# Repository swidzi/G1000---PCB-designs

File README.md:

# G1000 - PCB-desgins
PCB designes for G1000 Flight Sim controller STL (3d) files made by FlightSimMaker

This repository contains Eagle files for the PCB designed for G1000. All PCBs are millable on single sided clad with a 3018Pro CNC router.
Board design can be changed at anytime.
Boards are designed to be interconnected - if used separately they will probably not work.

# G1000 PFD/MFD PCB interconnection chart

# G1000 Audio PanelPCB interconnection chart

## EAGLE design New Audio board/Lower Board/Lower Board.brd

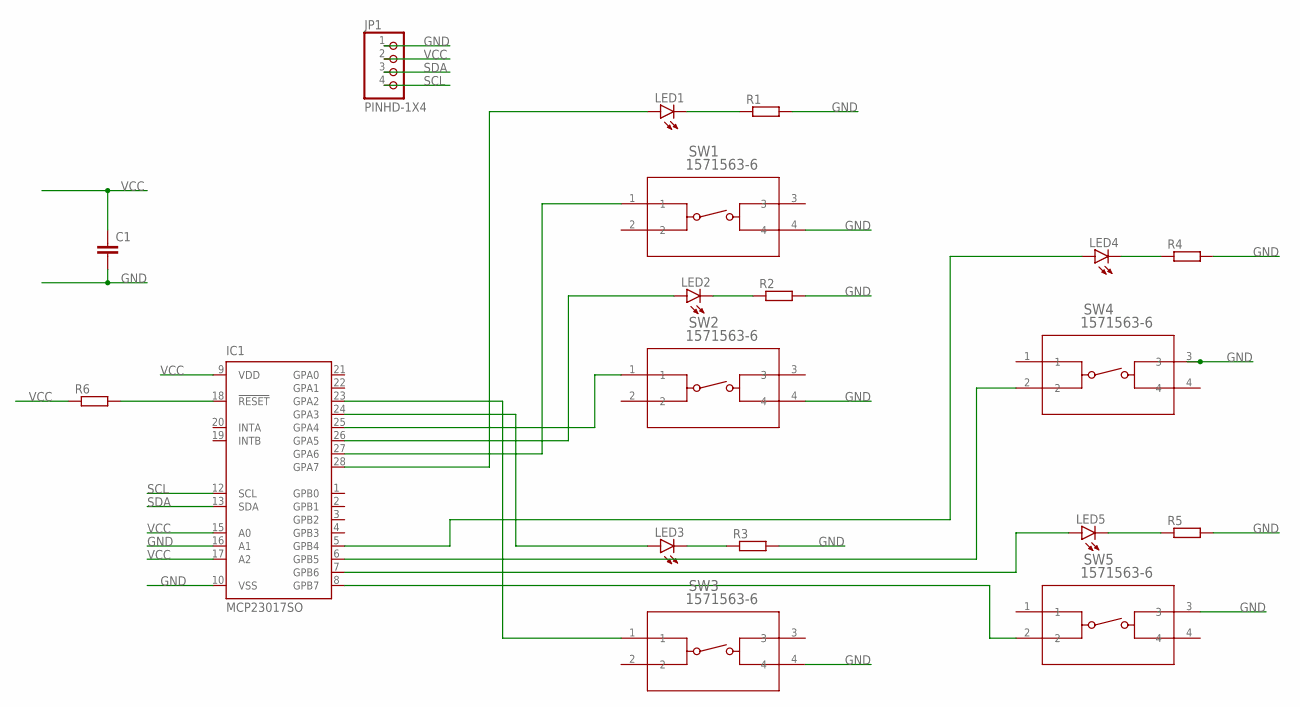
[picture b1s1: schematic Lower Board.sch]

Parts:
C1: C-EU025-025X050; C025-025X050
IC1: MCP23017SO; SO28W
JP1: PINHD-1X4; 1X04
LED1, LED2, LED3, LED4, LED5: LEDCHIP-LED0805; CHIP-LED0805
R1, R2, R3, R4, R5, R6: R-EU_R0805; R0805
SW1, SW2, SW3, SW4, SW5: 1571563-6; SW4_1437565-E

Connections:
GND: C1.2, IC1.10 (VSS), IC1.16 (A1), JP1.1, R1.2, R2.2, R3.2, R4.2, R5.2, SW1.4, SW2.4, SW3.4, SW4.3, SW5.3
unnamed: LED1.C, R1.1
unnamed: LED2.C, R2.1
unnamed: LED3.C, R3.1
unnamed: LED5.C, R5.1
unnamed: LED4.C, R4.1
unnamed: IC1.28 (GPA7), LED1.A
unnamed: IC1.27 (GPA6), SW1.1
unnamed: IC1.26 (GPA5), LED2.A
unnamed: IC1.25 (GPA4), SW2.1
unnamed: IC1.24 (GPA3), LED3.A
unnamed: IC1.23 (GPA2), SW3.1
unnamed: IC1.8 (GPB7), SW5.2
unnamed: IC1.18 (!RESET), R6.2
unnamed: IC1.7 (GPB6), LED5.A
unnamed: IC1.6 (GPB5), SW4.2
unnamed: IC1.5 (GPB4), LED4.A
SCL: IC1.12 (SCL), JP1.4
SDA: IC1.13 (SDA), JP1.3
VCC: C1.1, IC1.9 (VDD), IC1.15 (A0), IC1.17 (A2), JP1.2, R6.1

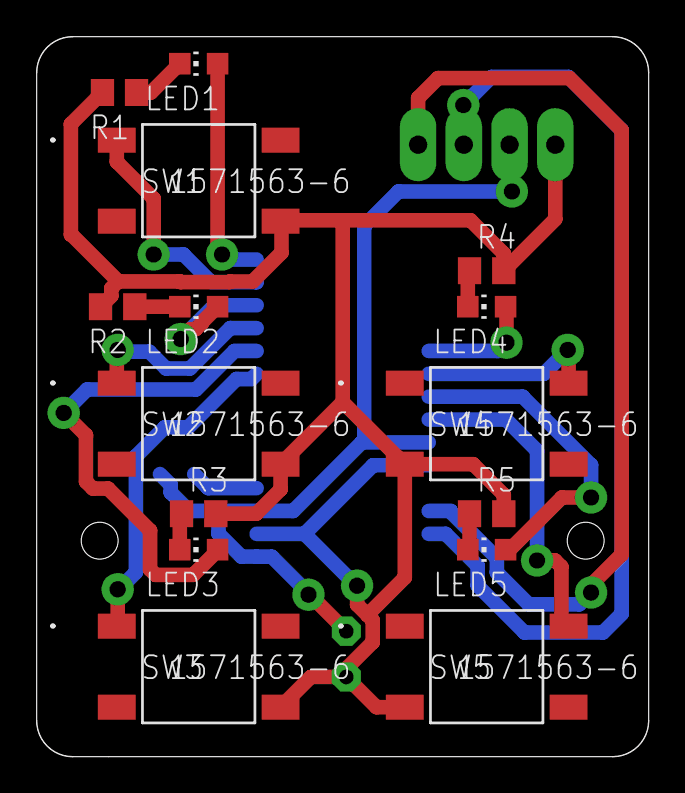
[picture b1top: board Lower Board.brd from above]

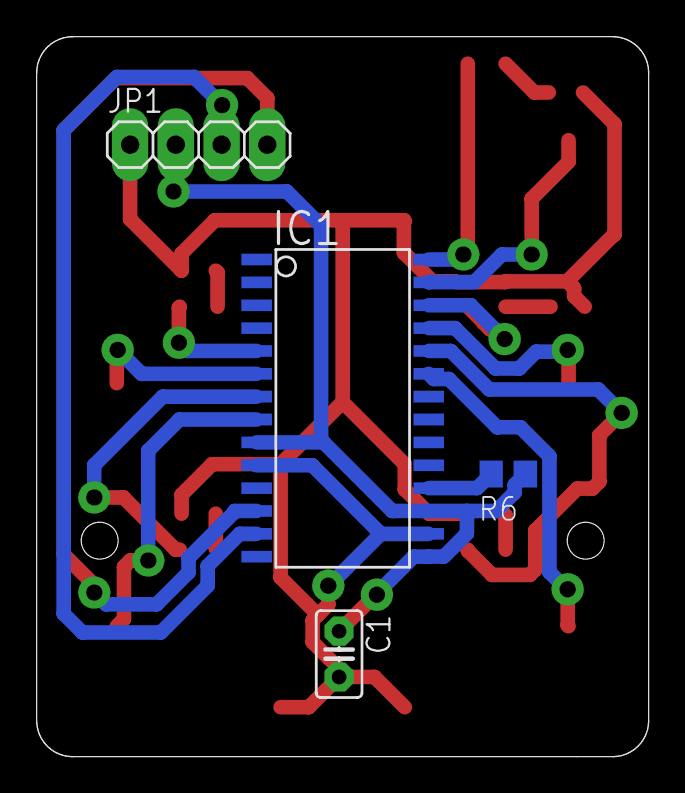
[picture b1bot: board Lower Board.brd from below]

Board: 2 copper layers, 34.0 x 40.0 mm, 19 parts (4 on the bottom side), 20 nets.

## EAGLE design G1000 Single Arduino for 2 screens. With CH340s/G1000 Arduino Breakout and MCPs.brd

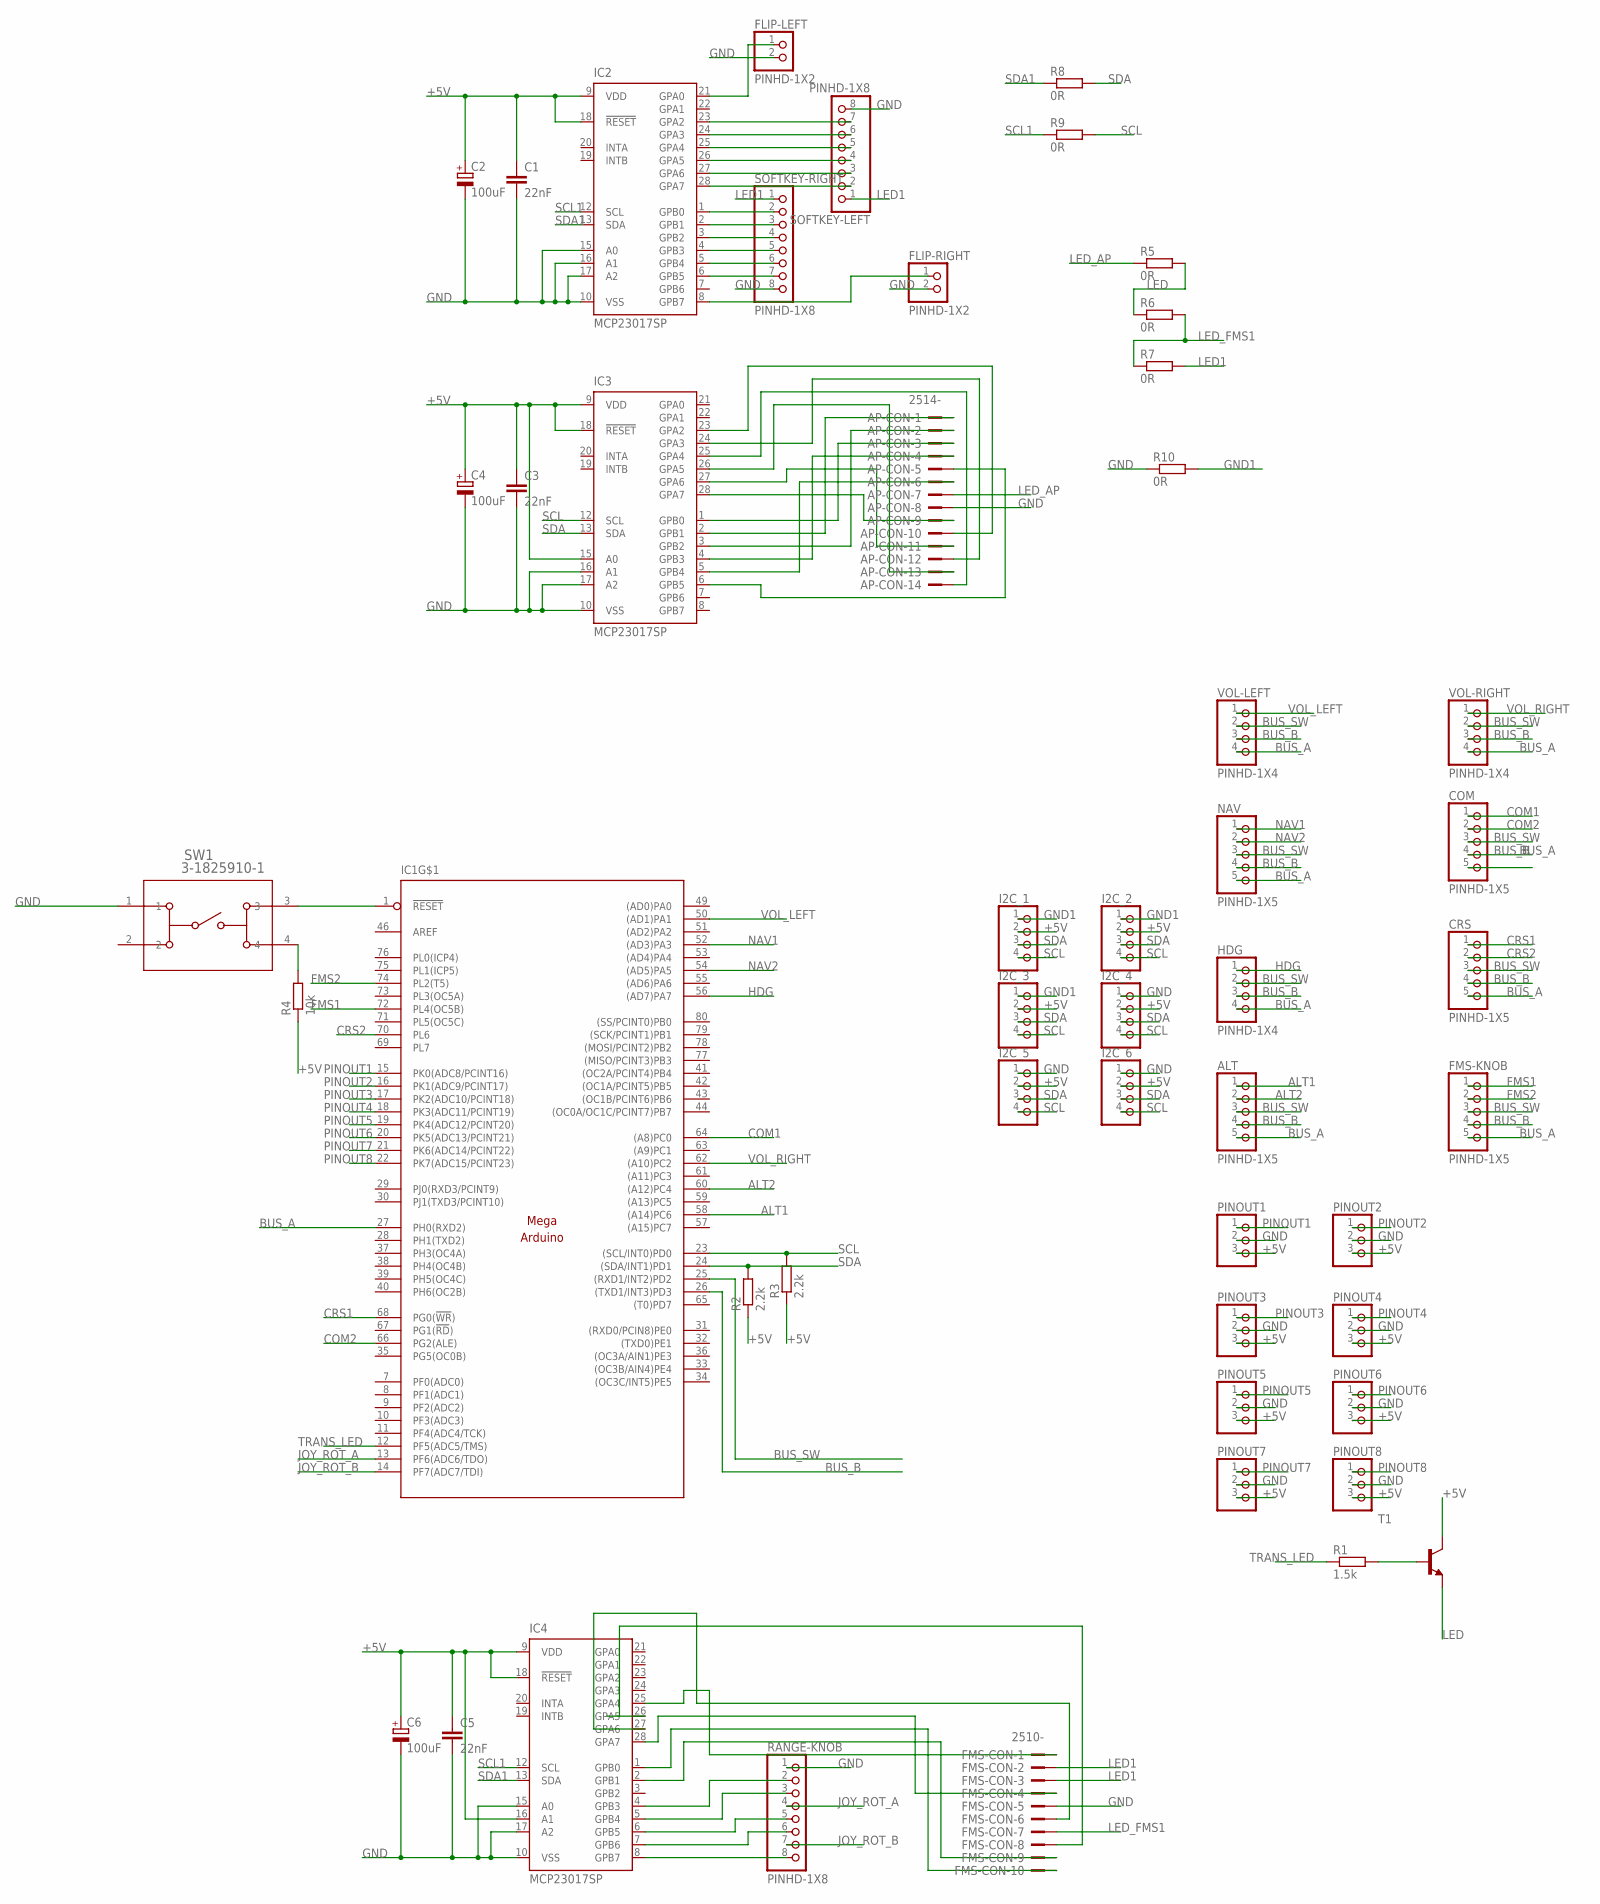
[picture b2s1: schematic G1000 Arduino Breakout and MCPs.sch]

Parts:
ALT: PINHD-1X5; 1X05
AP-CON: 2514-; PAK100/2500-14
C1, C3, C5: 22nF; C025-025X050
C2, C4, C6: 100uF; E2,5-6
COM: PINHD-1X5; 1X05
CRS: PINHD-1X5; 1X05
FLIP-LEFT: PINHD-1X2; 1X02
FLIP-RIGHT: PINHD-1X2; 1X02
FMS-CON: 2510-; PAK100/2500-10
FMS-KNOB: PINHD-1X5; 1X05
HDG: PINHD-1X4; 1X04
I2C_1, I2C_2, I2C_3, I2C_4, I2C_5, I2C_6: PINHD-1X4; 1X04
IC1: MEGAARDUINO_22; MEGA_ARDUINO_2
IC2, IC3, IC4: MCP23017SP; DIL28-3
NAV: PINHD-1X5; 1X05
PINOUT1, PINOUT2, PINOUT3, PINOUT4, PINOUT5, PINOUT6, PINOUT7, PINOUT8: PINHD-1X3; 1X03
R1: 1.5k; 0207/10
R2, R3: 2.2k; 0207/10
R4: 10k; 0207/10
R5, R6, R7, R8, R9, R10: 0R; 0207/10
RANGE-KNOB: PINHD-1X8; 1X08
SOFTKEY-LEFT: PINHD-1X8; 1X08
SOFTKEY-RIGHT: PINHD-1X8; 1X08
SW1: 3-1825910-1; SW4_1825910-H
T1: 2N2222-NPN-TO92-EBC; TO92-EBC
VOL-LEFT: PINHD-1X4; 1X04
VOL-RIGHT: PINHD-1X4; 1X04

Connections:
+3V3: IC1.2 (+3V3)
+5V: C1.1, C2.+, C3.1, C4.+, C5.1, C6.+, I2C_1.2, I2C_2.2, I2C_3.2, I2C_4.2, I2C_5.2, I2C_6.2, IC1.3 (+5V), IC1.47 (+5V), IC1.48 (+5V), IC2.9 (VDD), IC2.18 (!RESET), IC3.9 (VDD), IC3.15 (A0), IC3.18 (!RESET), IC4.9 (VDD), IC4.16 (A1), IC4.18 (!RESET), PINOUT1.3, PINOUT2.3, PINOUT3.3, PINOUT4.3, PINOUT5.3, PINOUT6.3, PINOUT7.3, PINOUT8.3, R2.1, R3.1, R4.1, T1.C
+VIN: IC1.6 (+VIN)
ALT1: ALT.1, IC1.58 ((A14)PC6)
ALT2: ALT.2, IC1.60 ((A12)PC4)
BUS_A: ALT.5, COM.5, CRS.5, FMS-KNOB.5, HDG.4, IC1.27 (PH0(RXD2)), NAV.5, VOL-LEFT.4, VOL-RIGHT.4
BUS_B: ALT.4, COM.4, CRS.4, FMS-KNOB.4, HDG.3, IC1.26 ((TXD1/INT3)PD3), NAV.4, VOL-LEFT.3, VOL-RIGHT.3
BUS_SW: ALT.3, COM.3, CRS.3, FMS-KNOB.3, HDG.2, IC1.25 ((RXD1/INT2)PD2), NAV.3, VOL-LEFT.2, VOL-RIGHT.2
COM1: COM.1, IC1.64 ((A8)PC0)
COM2: COM.2, IC1.66 (PG2(ALE))
CRS1: CRS.1, IC1.68 (PG0(!WR!))
CRS2: CRS.2, IC1.70 (PL6)
FMS1: FMS-KNOB.1, IC1.72 (PL4(OC5B))
FMS2: FMS-KNOB.2, IC1.74 (PL2(T5))
GND: AP-CON.8, C1.2, C2.-, C3.2, C4.-, C5.2, C6.-, FLIP-LEFT.2, FLIP-RIGHT.2, FMS-CON.5, I2C_4.1, I2C_5.1, I2C_6.1, IC1.4 (GND), IC1.5 (GND), IC1.45 (GND), IC1.81 (GND), IC1.82 (GND), IC2.10 (VSS), IC2.15 (A0), IC2.16 (A1), IC2.17 (A2), IC3.10 (VSS), IC3.16 (A1), IC3.17 (A2), IC4.10 (VSS), IC4.15 (A0), IC4.17 (A2), PINOUT1.2, PINOUT2.2, PINOUT3.2, PINOUT4.2, PINOUT5.2, PINOUT6.2, PINOUT7.2, PINOUT8.2, R10.1, RANGE-KNOB.1, SOFTKEY-LEFT.8, SOFTKEY-RIGHT.8, SW1.1
GND1: I2C_1.1, I2C_2.1, I2C_3.1, R10.2
HDG: HDG.1, IC1.56 ((AD7)PA7)
JOY_ROT_A: IC1.13 (PF6(ADC6/TDO)), RANGE-KNOB.4
JOY_ROT_B: IC1.14 (PF7(ADC7/TDI)), RANGE-KNOB.7
LED: R5.2, R6.1, T1.E
LED1: FMS-CON.2, FMS-CON.3, R7.2, SOFTKEY-LEFT.1, SOFTKEY-RIGHT.1
LED_AP: AP-CON.7, R5.1
LED_FMS1: FMS-CON.7, R6.2, R7.1
unnamed: R1.2, T1.B
unnamed: IC2.1 (GPB0), SOFTKEY-RIGHT.2
unnamed: IC2.2 (GPB1), SOFTKEY-RIGHT.3
unnamed: IC2.3 (GPB2), SOFTKEY-RIGHT.4
unnamed: IC2.4 (GPB3), SOFTKEY-RIGHT.5
unnamed: IC2.5 (GPB4), SOFTKEY-RIGHT.6
unnamed: IC2.6 (GPB5), SOFTKEY-RIGHT.7
unnamed: IC2.28 (GPA7), SOFTKEY-LEFT.2
unnamed: IC2.27 (GPA6), SOFTKEY-LEFT.3
unnamed: IC2.26 (GPA5), SOFTKEY-LEFT.4
unnamed: IC2.25 (GPA4), SOFTKEY-LEFT.5
unnamed: IC2.24 (GPA3), SOFTKEY-LEFT.6
unnamed: IC2.23 (GPA2), SOFTKEY-LEFT.7
unnamed: FLIP-LEFT.1, IC2.21 (GPA0)
unnamed: FLIP-RIGHT.1, IC2.8 (GPB7)
unnamed: R4.2, SW1.4
unnamed: AP-CON.3, IC3.1 (GPB0)
unnamed: IC1.1 (!RESET), SW1.3
unnamed: AP-CON.1, IC3.2 (GPB1)
unnamed: AP-CON.2, IC3.3 (GPB2)
unnamed: AP-CON.4, IC3.4 (GPB3)
unnamed: AP-CON.6, IC3.5 (GPB4)
unnamed: AP-CON.9, IC3.28 (GPA7)
unnamed: AP-CON.11, IC3.27 (GPA6)
unnamed: AP-CON.13, IC3.26 (GPA5)
unnamed: AP-CON.14, IC3.25 (GPA4)
unnamed: AP-CON.12, IC3.24 (GPA3)
unnamed: AP-CON.10, IC3.23 (GPA2)
unnamed: AP-CON.5, IC3.6 (GPB5)
unnamed: IC4.8 (GPB7), RANGE-KNOB.8
unnamed: IC4.7 (GPB6), RANGE-KNOB.6
unnamed: IC4.6 (GPB5), RANGE-KNOB.5
unnamed: IC4.5 (GPB4), RANGE-KNOB.3
unnamed: IC4.4 (GPB3), RANGE-KNOB.2
unnamed: FMS-CON.1, IC4.25 (GPA4)
unnamed: FMS-CON.9, IC4.2 (GPB1)
unnamed: FMS-CON.10, IC4.1 (GPB0)
unnamed: FMS-CON.4, IC4.28 (GPA7)
unnamed: FMS-CON.6, IC4.27 (GPA6)
unnamed: FMS-CON.8, IC4.26 (GPA5)
NAV1: IC1.52 ((AD3)PA3), NAV.1
NAV2: IC1.54 ((AD5)PA5), NAV.2
PINOUT1: IC1.15 (PK0(ADC8/PCINT16)), PINOUT1.1
PINOUT2: IC1.16 (PK1(ADC9/PCINT17)), PINOUT2.1
PINOUT3: IC1.17 (PK2(ADC10/PCINT18)), PINOUT3.1
PINOUT4: IC1.18 (PK3(ADC11/PCINT19)), PINOUT4.1
PINOUT5: IC1.19 (PK4(ADC12/PCINT20)), PINOUT5.1
PINOUT6: IC1.20 (PK5(ADC13/PCINT21)), PINOUT6.1
PINOUT7: IC1.21 (PK6(ADC14/PCINT22)), PINOUT7.1
PINOUT8: IC1.22 (PK7(ADC15/PCINT23)), PINOUT8.1
SCL: I2C_1.4, I2C_2.4, I2C_3.4, I2C_4.4, I2C_5.4, I2C_6.4, IC1.23 ((SCL/INT0)PD0), IC3.12 (SCL), R3.2, R9.2
SCL1: IC2.12 (SCL), IC4.12 (SCL), R9.1
SDA: I2C_1.3, I2C_2.3, I2C_3.3, I2C_4.3, I2C_5.3, I2C_6.3, IC1.24 ((SDA/INT1)PD1), IC3.13 (SDA), R2.2, R8.2
SDA1: IC2.13 (SDA), IC4.13 (SDA), R8.1
TRANS_LED: IC1.12 (PF5(ADC5/TMS)), R1.1
VOL_LEFT: IC1.50 ((AD1)PA1), VOL-LEFT.1
VOL_RIGHT: IC1.62 ((A10)PC2), VOL-RIGHT.1

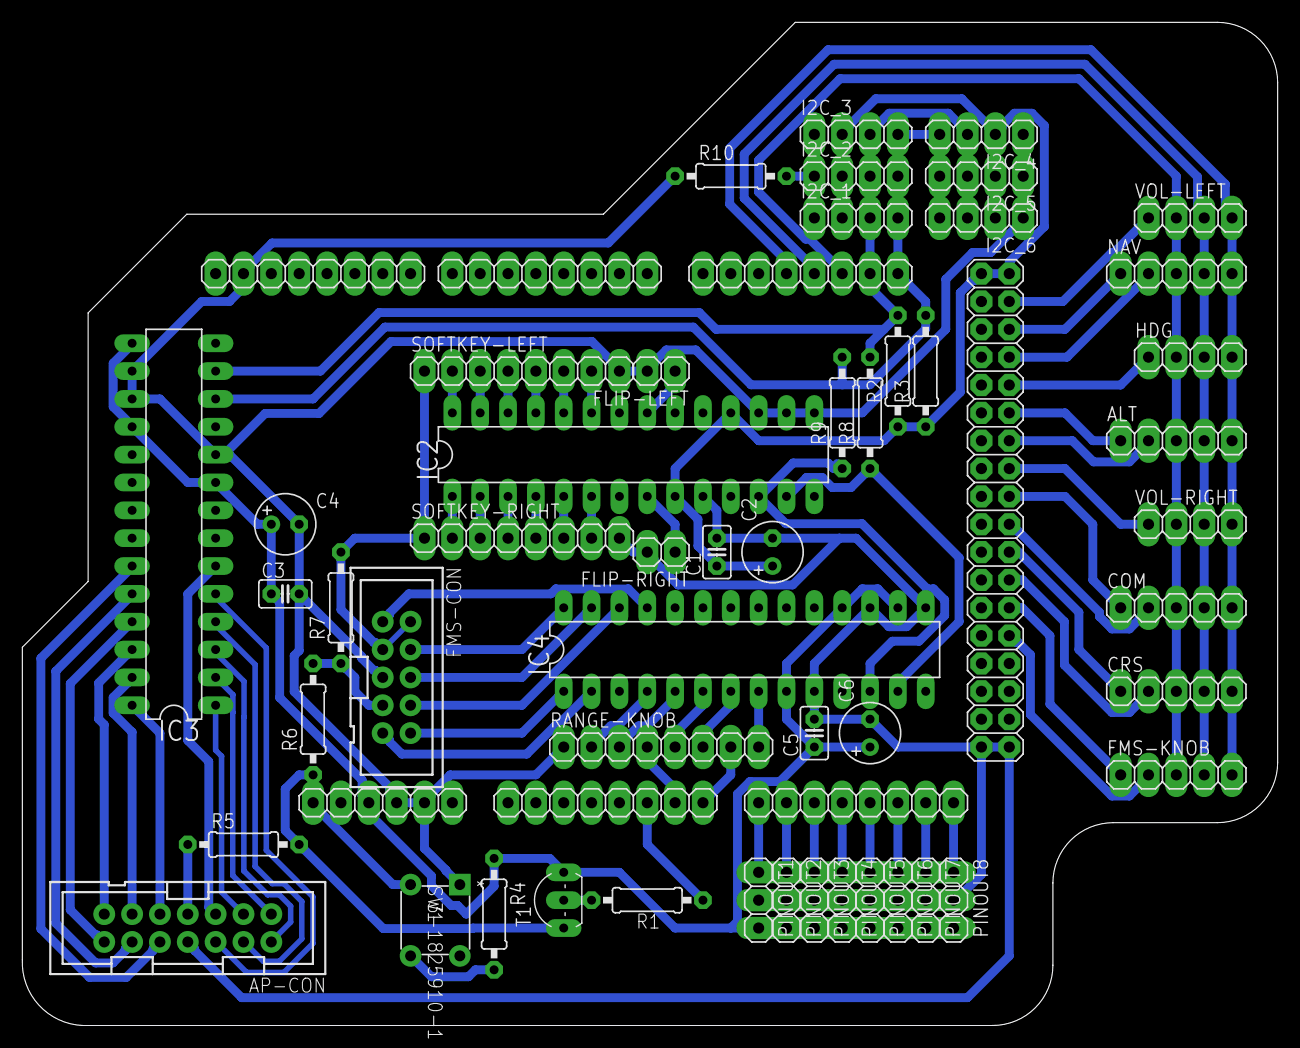
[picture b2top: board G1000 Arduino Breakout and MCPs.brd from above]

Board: 2 copper layers, 114.5 x 91.5 mm, 51 parts (0 on the bottom side), 78 nets.

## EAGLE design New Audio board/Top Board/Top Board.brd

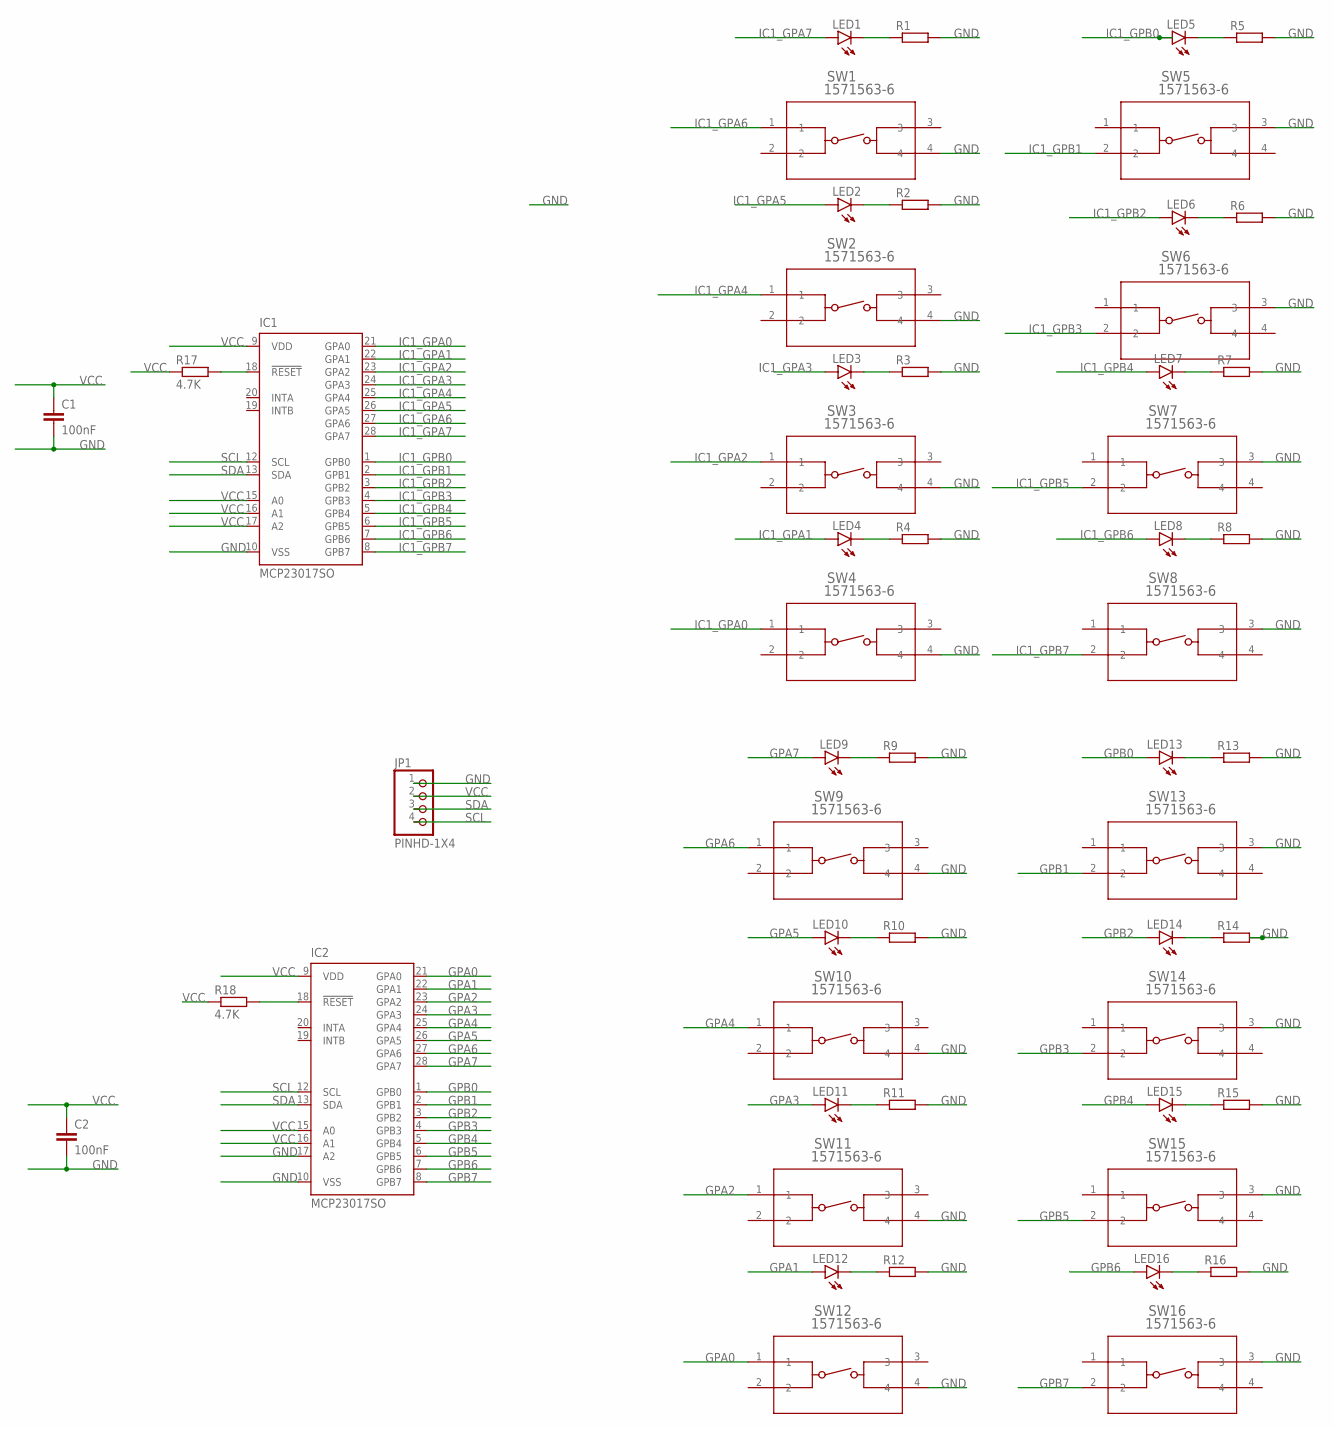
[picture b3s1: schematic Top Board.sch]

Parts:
C1, C2: 100nF; C025-025X050
IC1, IC2: MCP23017SO; SO28W
JP1: PINHD-1X4; 1X04
LED1, LED2, LED3, LED4, LED5, LED6, LED7, LED8, LED9, LED10, LED11, LED12, LED13, LED14, LED15, LED16: LEDCHIP-LED0805; CHIP-LED0805
R1, R2, R3, R4, R5, R6, R7, R8, R9, R10, R11, R12, R13, R14, R15, R16: R-EU_R0805; R0805
R17, R18: 4.7K; R0805
SW1, SW2, SW3, SW4, SW5, SW6, SW7, SW8, SW9, SW10, SW11, SW12, SW13, SW14, SW15, SW16: 1571563-6; SW4_1437565-E

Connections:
GND: C1.2, C2.2, IC1.10 (VSS), IC2.10 (VSS), IC2.17 (A2), JP1.1, R1.2, R2.2, R3.2, R4.2, R5.2, R6.2, R7.2, R8.2, R9.2, R10.2, R11.2, R12.2, R13.2, R14.2, R15.2, R16.2, SW1.4, SW2.4, SW3.4, SW4.4, SW5.3, SW6.3, SW7.3, SW8.3, SW9.4, SW10.4, SW11.4, SW12.4, SW13.3, SW14.3, SW15.3, SW16.3
GPA0: IC2.21 (GPA0), SW12.1
GPA1: IC2.22 (GPA1), LED12.A
GPA2: IC2.23 (GPA2), SW11.1
GPA3: IC2.24 (GPA3), LED11.A
GPA4: IC2.25 (GPA4), SW10.1
GPA5: IC2.26 (GPA5), LED10.A
GPA6: IC2.27 (GPA6), SW9.1
GPA7: IC2.28 (GPA7), LED9.A
GPB0: IC2.1 (GPB0), LED13.A
GPB1: IC2.2 (GPB1), SW13.2
GPB2: IC2.3 (GPB2), LED14.A
GPB3: IC2.4 (GPB3), SW14.2
GPB4: IC2.5 (GPB4), LED15.A
GPB5: IC2.6 (GPB5), SW15.2
GPB6: IC2.7 (GPB6), LED16.A
GPB7: IC2.8 (GPB7), SW16.2
IC1_GPA0: IC1.21 (GPA0), SW4.1
IC1_GPA1: IC1.22 (GPA1), LED4.A
IC1_GPA2: IC1.23 (GPA2), SW3.1
IC1_GPA3: IC1.24 (GPA3), LED3.A
IC1_GPA4: IC1.25 (GPA4), SW2.1
IC1_GPA5: IC1.26 (GPA5), LED2.A
IC1_GPA6: IC1.27 (GPA6), SW1.1
IC1_GPA7: IC1.28 (GPA7), LED1.A
IC1_GPB0: IC1.1 (GPB0), LED5.A
IC1_GPB1: IC1.2 (GPB1), SW5.2
IC1_GPB2: IC1.3 (GPB2), LED6.A
IC1_GPB3: IC1.4 (GPB3), SW6.2
IC1_GPB4: IC1.5 (GPB4), LED7.A
IC1_GPB5: IC1.6 (GPB5), SW7.2
IC1_GPB6: IC1.7 (GPB6), LED8.A
IC1_GPB7: IC1.8 (GPB7), SW8.2
unnamed: LED1.C, R1.1
unnamed: LED2.C, R2.1
unnamed: LED3.C, R3.1
unnamed: LED4.C, R4.1
unnamed: LED5.C, R5.1
unnamed: LED6.C, R6.1
unnamed: LED7.C, R7.1
unnamed: LED8.C, R8.1
unnamed: LED9.C, R9.1
unnamed: LED10.C, R10.1
unnamed: LED11.C, R11.1
unnamed: LED12.C, R12.1
unnamed: LED13.C, R13.1
unnamed: LED14.C, R14.1
unnamed: LED15.C, R15.1
unnamed: LED16.C, R16.1
unnamed: IC2.18 (!RESET), R18.2
unnamed: IC1.18 (!RESET), R17.2
SCL: IC1.12 (SCL), IC2.12 (SCL), JP1.4
SDA: IC1.13 (SDA), IC2.13 (SDA), JP1.3
VCC: C1.1, C2.1, IC1.9 (VDD), IC1.15 (A0), IC1.16 (A1), IC1.17 (A2), IC2.9 (VDD), IC2.15 (A0), IC2.16 (A1), JP1.2, R17.1, R18.1

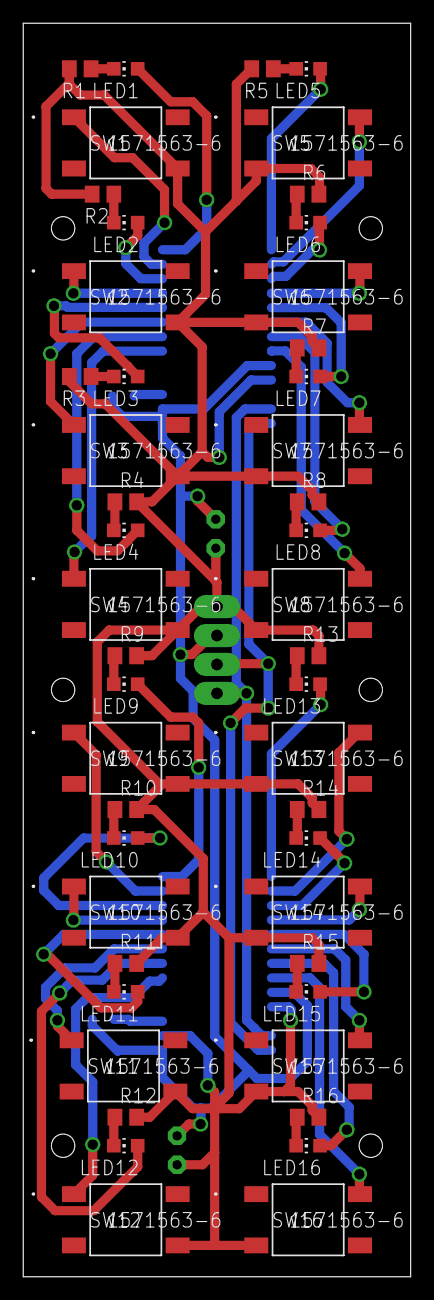
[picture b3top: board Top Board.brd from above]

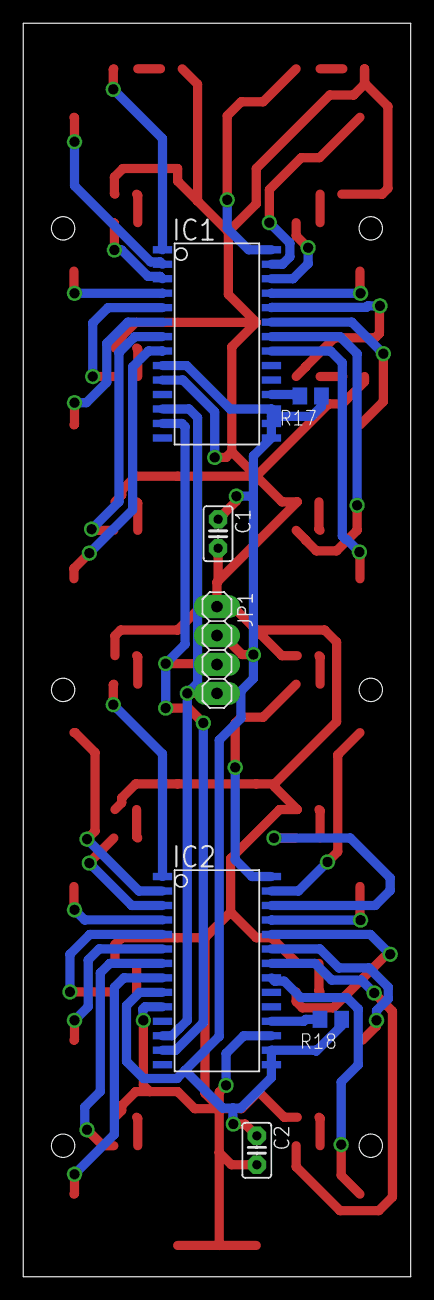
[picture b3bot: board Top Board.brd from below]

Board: 2 copper layers, 34.0 x 110.0 mm, 55 parts (7 on the bottom side), 54 nets.

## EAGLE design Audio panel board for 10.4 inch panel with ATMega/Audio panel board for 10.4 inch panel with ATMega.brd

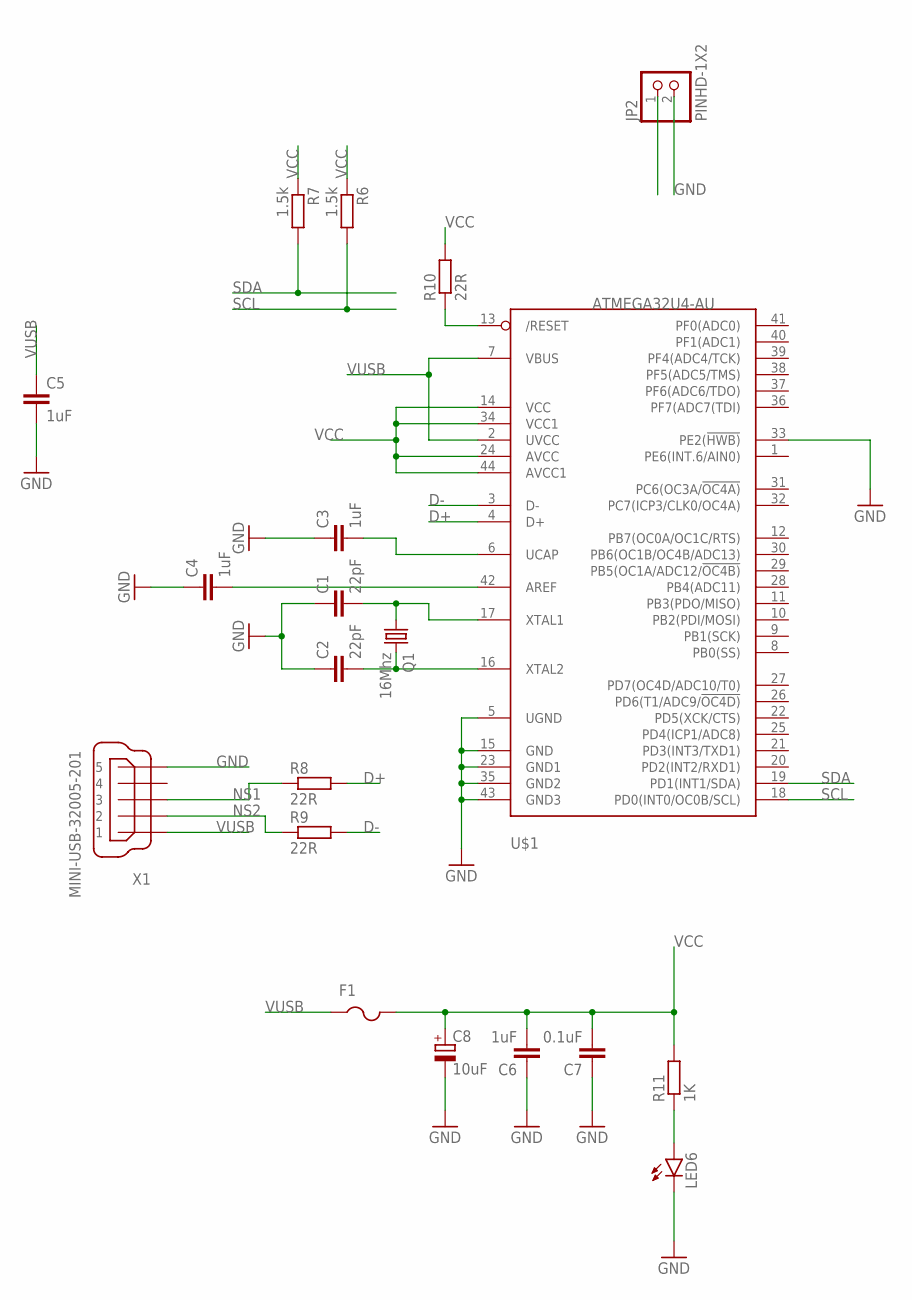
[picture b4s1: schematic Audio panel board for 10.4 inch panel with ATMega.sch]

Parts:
C1, C2: 22pF; C025-025X050
C3, C4, C5, C6: 1uF; C025-025X050
C7: 0.1uF; C025-025X050
C8: 10uF; E2,5-7
F1: PTCFUSE-1206; R1206
JP2: PINHD-1X2; 1X02
LED6: LEDCHIP-LED0805; CHIP-LED0805
Q1: 16Mhz; HC49/S
R6, R7: 1.5k; R0805
R8, R9, R10: 22R; R0805
R11: 1K; R0805
U$1: ATMEGA32U4-AU; TQFP44
X1: MINI-USB-32005-201; 32005-201

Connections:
D+: R8.2, U$1.4 (D+)
D-: R9.2, U$1.3 (D-)
GND: C1.1, C2.1, C3.1, C4.1, C5.2, C6.1, C7.1, C8.-, JP2.2, LED6.C, U$1.5 (UGND), U$1.15 (GND), U$1.23 (GND1), U$1.33 (PE2(!HWB)), U$1.35 (GND2), U$1.43 (GND3), X1.5
unnamed: C4.2, U$1.42 (AREF)
unnamed: C2.2, Q1.2, U$1.16 (XTAL2)
unnamed: C1.2, Q1.1, U$1.17 (XTAL1)
unnamed: C3.2, U$1.6 (UCAP)
unnamed: R10.1, U$1.13 (/RESET)
unnamed: LED6.A, R11.1
NS1: R8.1, X1.3
NS2: R9.1, X1.2
SCL: R6.2, U$1.18 (PD0(INT0/OC0B/SCL))
SDA: R7.2, U$1.19 (PD1(INT1/SDA))
VCC: C6.2, C7.2, C8.+, F1.2, R6.1, R7.1, R10.2, R11.2, U$1.14 (VCC), U$1.24 (AVCC), U$1.34 (VCC1), U$1.44 (AVCC1)
VUSB: C5.1, F1.1, U$1.2 (UVCC), U$1.7 (VBUS), X1.1

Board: 2 copper layers, 20 parts (1 on the bottom side), 15 nets, no tracks yet.

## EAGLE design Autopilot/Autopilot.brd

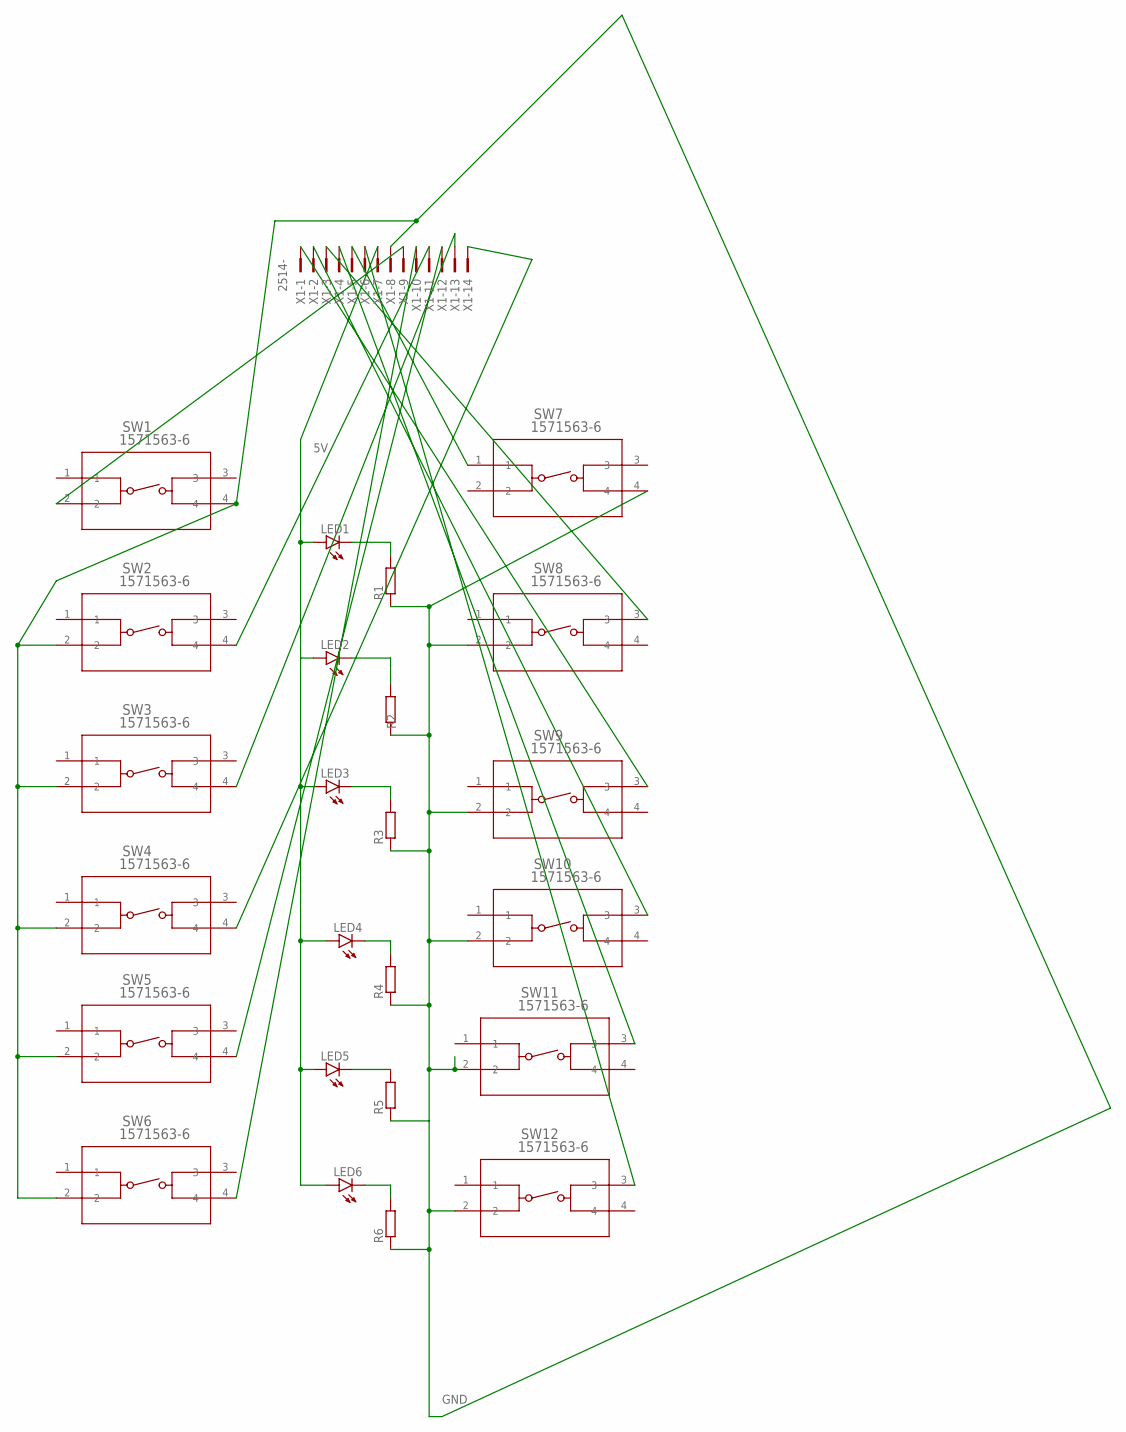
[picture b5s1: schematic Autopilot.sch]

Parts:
LED1, LED2, LED3, LED4, LED5, LED6: LEDCHIPLED_1206; CHIPLED_1206
R1, R2, R3, R4, R5, R6: R-EU_R1206; R1206
SW1, SW2, SW3, SW4, SW5, SW6, SW7, SW8, SW9, SW10, SW11, SW12: 1571563-6; SW4_1437565-E
X1: 2514-; PAK100/2500-14

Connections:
5V: LED1.A, LED2.A, LED3.A, LED4.A, LED5.A, LED6.A, X1.7
GND: R1.1, R2.1, R3.1, R4.1, R5.1, R6.1, SW1.4, SW2.2, SW3.2, SW4.2, SW5.2, SW6.2, SW7.4, SW8.2, SW9.2, SW10.2, SW11.2, SW12.2, X1.8
unnamed: LED1.C, R1.2
unnamed: LED2.C, R2.2
unnamed: LED3.C, R3.2
unnamed: LED4.C, R4.2
unnamed: LED5.C, R5.2
unnamed: LED6.C, R6.2
unnamed: SW1.2, X1.9
unnamed: SW7.1, X1.5
unnamed: SW8.3, X1.3
unnamed: SW9.3, X1.1
unnamed: SW10.3, X1.2
unnamed: SW11.3, X1.4
unnamed: SW12.3, X1.6
unnamed: SW2.4, X1.11
unnamed: SW4.4, X1.14
unnamed: SW3.4, X1.13
unnamed: SW5.4, X1.12
unnamed: SW6.4, X1.10

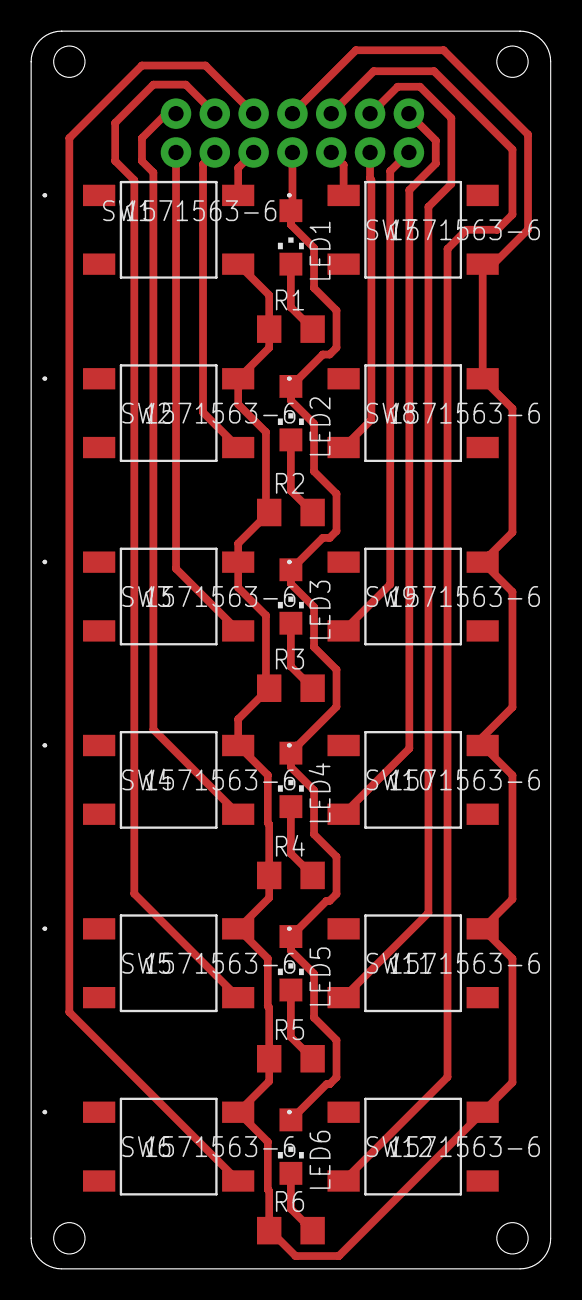
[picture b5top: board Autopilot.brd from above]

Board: 2 copper layers, 34.0 x 81.0 mm, 25 parts (1 on the bottom side), 20 nets.

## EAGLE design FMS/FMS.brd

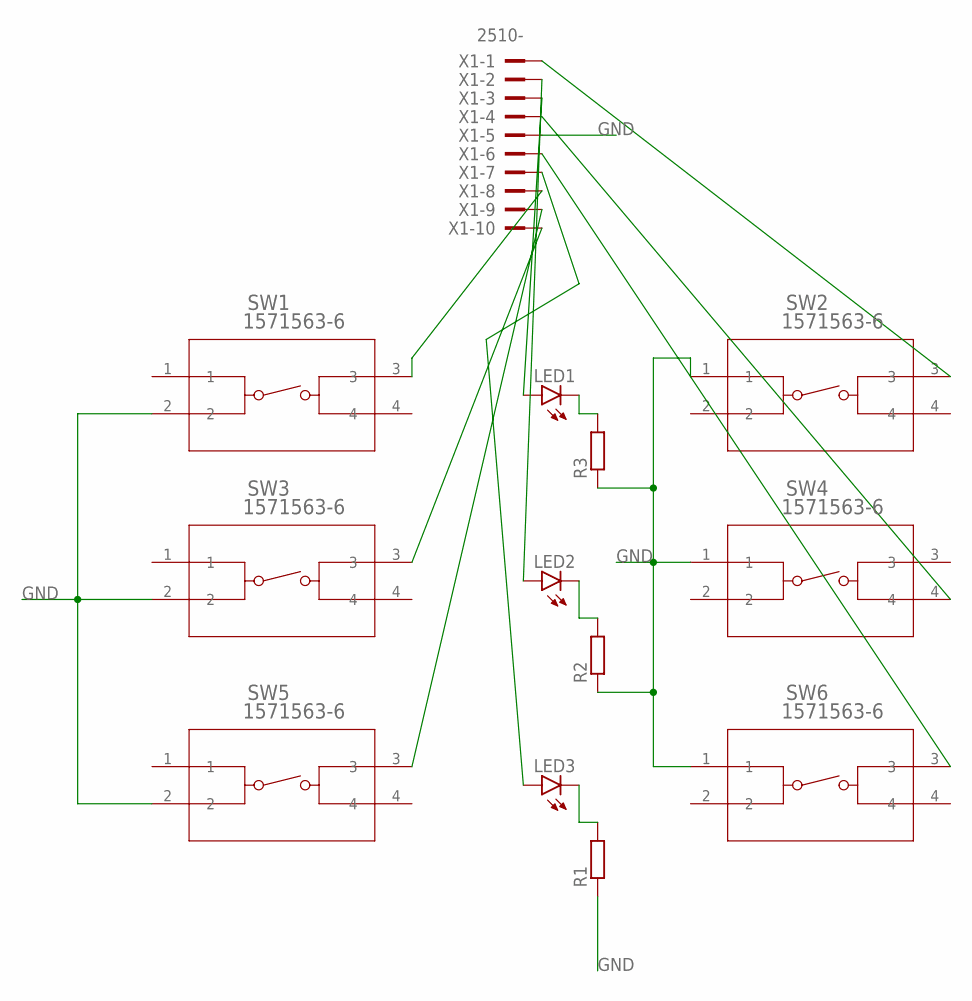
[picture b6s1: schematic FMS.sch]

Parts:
LED1, LED2, LED3: LEDCHIPLED_1206; CHIPLED_1206
R1, R2, R3: R-EU_R1206; R1206
SW1, SW2, SW3, SW4, SW5, SW6: 1571563-6; SW4_1437565-E
X1: 2510-; PAK100/2500-10

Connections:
GND: R1.1, R2.1, R3.1, SW1.2, SW2.1, SW3.2, SW4.1, SW5.2, SW6.1, X1.5
unnamed: LED1.A, X1.3
unnamed: SW2.3, X1.1
unnamed: LED2.A, X1.2
unnamed: LED1.C, R3.2
unnamed: LED2.C, R2.2
unnamed: LED3.C, R1.2
unnamed: SW4.4, X1.4
unnamed: SW6.3, X1.6
unnamed: LED3.A, X1.7
unnamed: SW1.3, X1.8
unnamed: SW3.3, X1.10
unnamed: SW5.3, X1.9

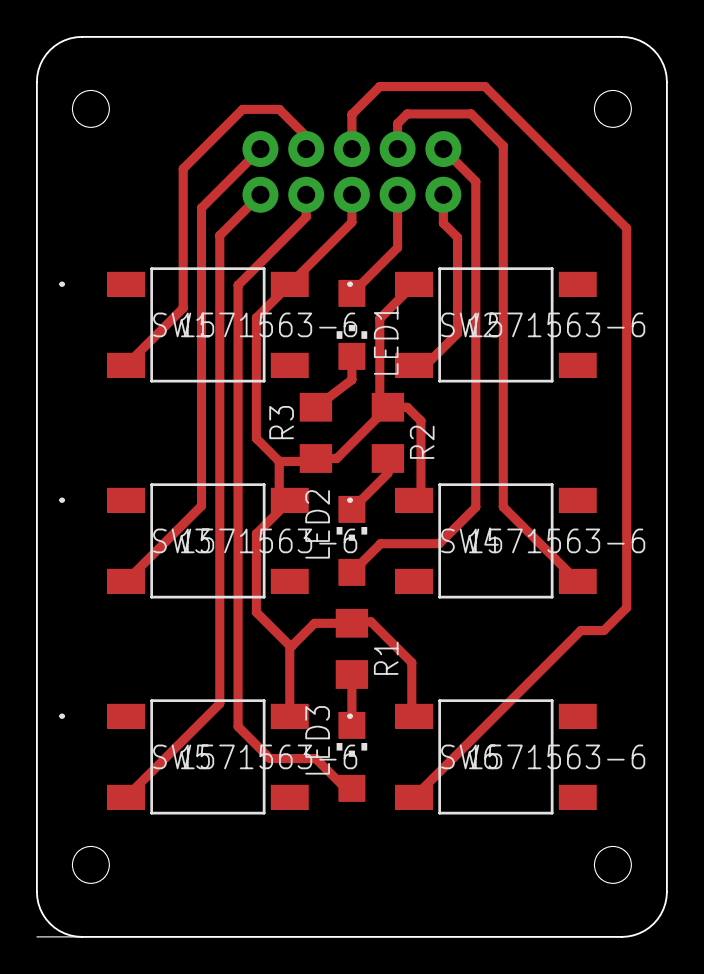
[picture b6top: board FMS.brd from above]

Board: 2 copper layers, 35.0 x 50.0 mm, 13 parts (1 on the bottom side), 13 nets.

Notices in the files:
parts and their libraries:
COPYRIGHT: Copyright (C) 2016 Accelerated Designs. All rights reserved
